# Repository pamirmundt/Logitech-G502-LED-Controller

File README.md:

# Logitech G502 Mouse with Python
A dirty code where you can set Logitech G502 mouse led color and read click/position events with Python. The USB packages send from the PC driver and mouse sniffed with USBlyzer software on a Windows machine. Attached demo codes tested only on a Raspberry Pi 3 (Raspbian). Sniffed files can be found under the USBlyzer folder. `interrupt.ulz` file has interrupt packages and `firstPlug.ulz` file has first time USB plug packages.

There are two interfaces under mouse:

#### Interface 0: Mouse Device
 - Get interrupt events (cursor move, click, wheel and etc.)

#### Interface 1: Keyboard Device (I guess)
 - Set RGB LED colors (Logo LED and DPI LED)

### Notes:
- Interrupt events should be read (Interface-0) continuously. Otherwise mouse buffer fills and you cannot send any more data to Interface-1.

## Board and Schematics
The system consists of 3 different boards: (1) Arduino UNO, (2)USB Host Shield 2.0 and (3)a custom LED controller/power supply board.

|     Layer     | Board Name                          | Board Description                   |
| ------------- | ----------------------------------- | ----------------------------------- |
|  1(bottom)    | Arduino UNO                         | MCU                                 |
|  2(middle)    | USB Host Shield 2.0                 | USB Controller in Host Mode         |
|  3(top)       | LED Controller and Power Supply (*) | RGB Led controller and 5V regulator |

(*) Eagle CAD files (.brd, .sch) can be found in the repo

## Future Improvements
- [ ] Switching regulator for 5V
- [ ] Single board layout
- [ ] Inconsistent color transitions between LED strip and G502 LEDs

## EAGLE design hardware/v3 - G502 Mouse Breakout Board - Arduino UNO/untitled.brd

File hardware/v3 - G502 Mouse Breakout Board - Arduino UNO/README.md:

## V3 G502 Breakout Board
- RGB Led Strip Controller Board for Arduino UNO
- 8-18V Input
- 5V regulator to supply Arduino UNO and USB Host Shield 2.0

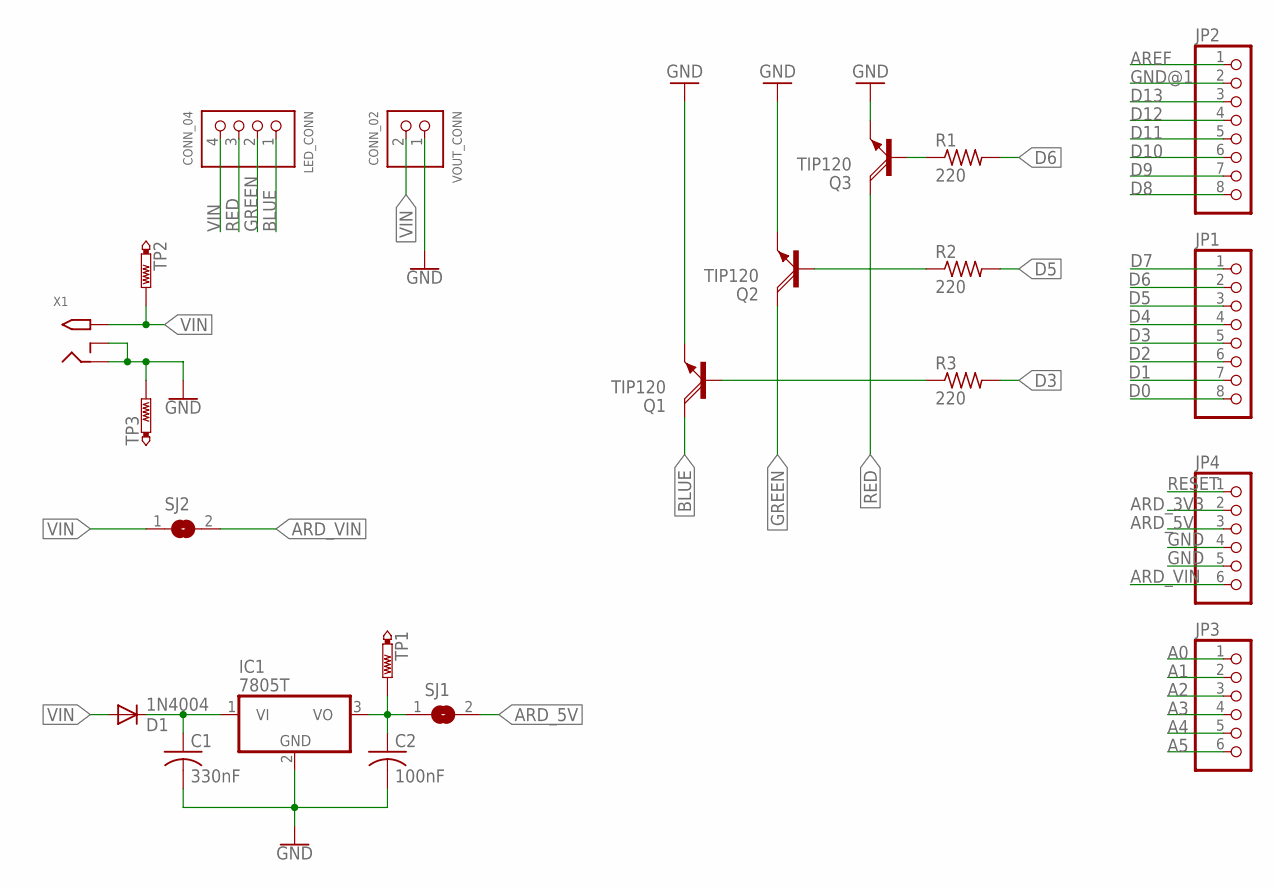
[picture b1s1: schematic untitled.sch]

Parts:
C1: 330nF; C050-035X075
C2: 100nF; C050-035X075
D1: 1N4004; DO41-10
IC1: 7805T; TO220H
JP1, JP2: PINHD-1X8; 1X08
JP3, JP4: PINHD-1X6; 1X06
LED_CONN: CONN_04; SCREWTERMINAL-5MM-4
Q1, Q2, Q3: TIP120; TO220AH
R1, R2, R3: 220; 0207/9
SJ1, SJ2: SJ
TP1, TP2, TP3: PTR1B1,27; B1,27
VOUT_CONN: CONN_02; SCREWTERMINAL-5MM-2
X1: 2.1MMJACKTHM; PJ-102A

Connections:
A0: JP3.1
A1: JP3.2
A2: JP3.3
A3: JP3.4
A4: JP3.5
A5: JP3.6
ARD_3V3: JP4.2
ARD_5V: JP4.3, SJ1.2
ARD_VIN: JP4.6, SJ2.2
AREF: JP2.1
BLUE: LED_CONN.1, Q1.C
D0: JP1.8
D1: JP1.7
D2: JP1.6
D3: JP1.5, R3.2
D4: JP1.4
D5: JP1.3, R2.2
D6: JP1.2, R1.2
D7: JP1.1
D8: JP2.8
D9: JP2.7
D10: JP2.6
D11: JP2.5
D12: JP2.4
D13: JP2.3
GND: C1.2, C2.2, IC1.2 (GND), JP4.4, JP4.5, Q1.E, Q2.E, Q3.E, TP3.TP, VOUT_CONN.1, X1.RING, X1.RING_SW
GND@1: JP2.2
GREEN: LED_CONN.2, Q2.C
unnamed: C1.1, D1.C, IC1.1 (VI)
unnamed: Q3.B, R1.1
unnamed: Q2.B, R2.1
unnamed: Q1.B, R3.1
RED: LED_CONN.3, Q3.C
REG_5V: C2.1, IC1.3 (VO), SJ1.1, TP1.TP
RESET: JP4.1
VIN: D1.A, LED_CONN.4, SJ2.1, TP2.TP, VOUT_CONN.2, X1.TIP

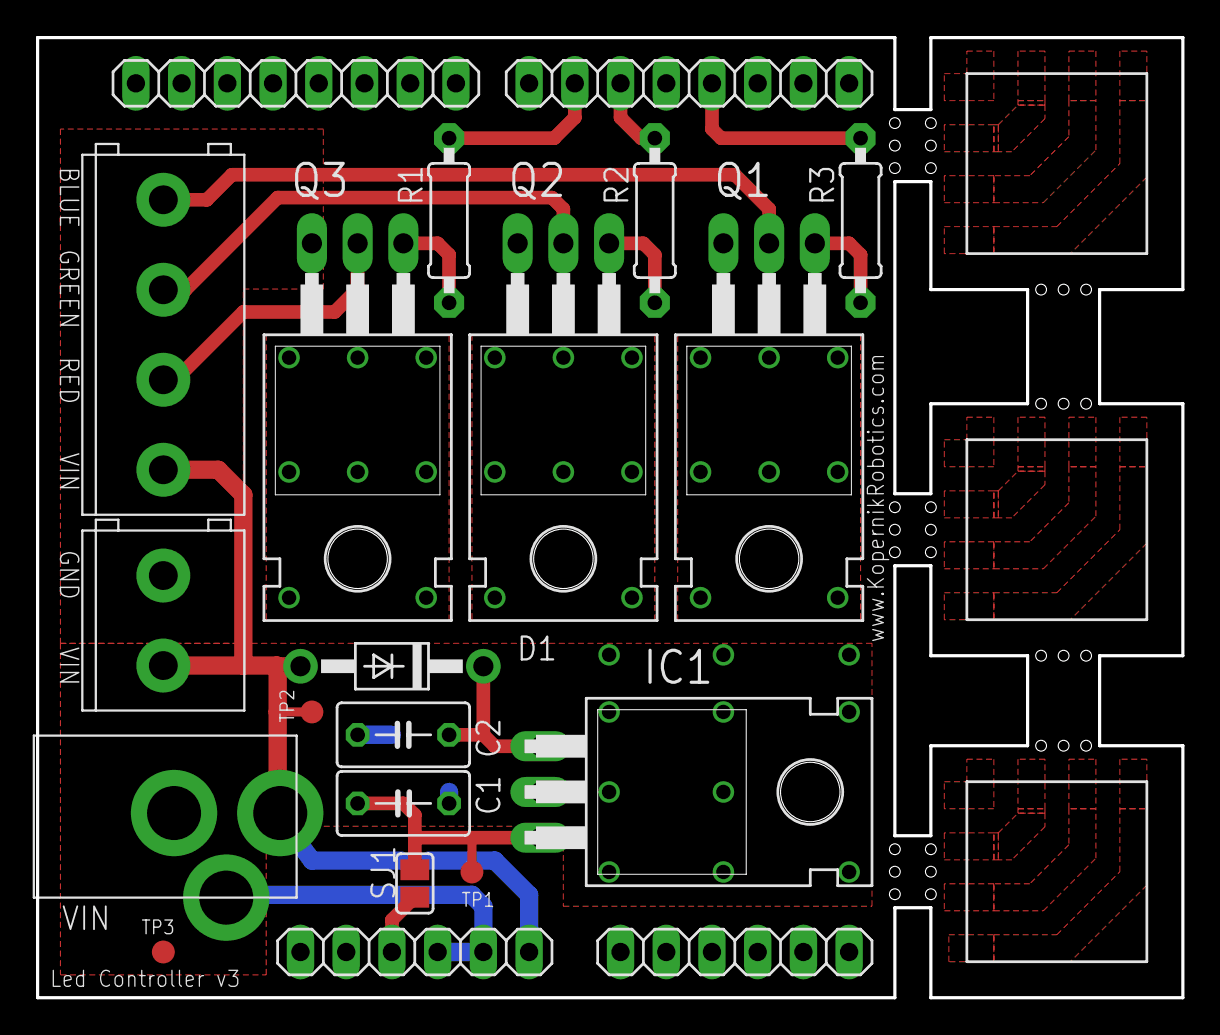
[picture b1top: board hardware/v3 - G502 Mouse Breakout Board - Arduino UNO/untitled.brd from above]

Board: 2 copper layers, 63.6 x 53.3 mm, 22 parts (1 on the bottom side), 15 nets.

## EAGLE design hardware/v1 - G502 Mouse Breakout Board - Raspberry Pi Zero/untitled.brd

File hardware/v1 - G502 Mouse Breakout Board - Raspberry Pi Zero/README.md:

## V1 G502 Breakout Board
- RGB Led Strip Controller Board for Raspberry Pi Zero

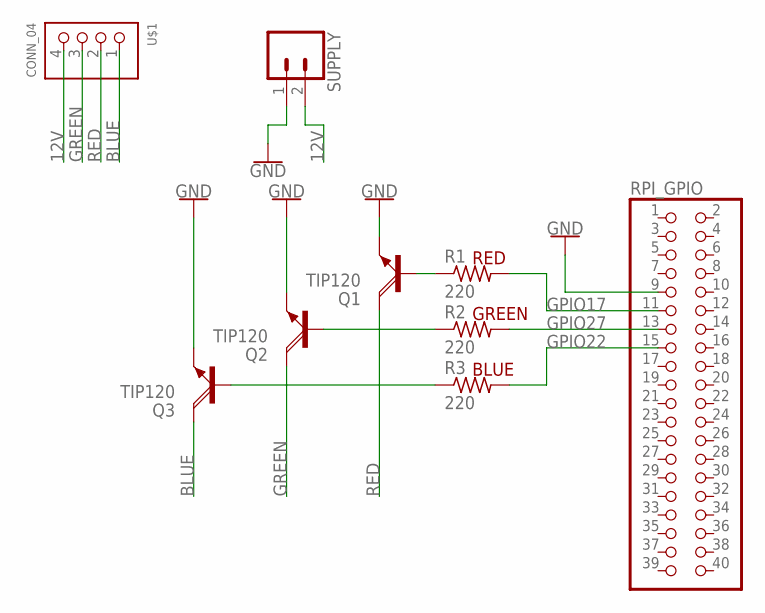
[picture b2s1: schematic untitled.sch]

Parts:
Q1, Q2, Q3: TIP120; TO220AH
R1, R2, R3: 220; 0207/10
RPI_GPIO: PINHD-2X20; 2X20
SUPPLY: CONN_025MM; SCREWTERMINAL-5MM-2
U$1: CONN_04; SCREWTERMINAL-5MM-4

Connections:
12V: SUPPLY.2, U$1.4
BLUE: Q3.C, U$1.1
GND: Q1.E, Q2.E, Q3.E, RPI_GPIO.9, SUPPLY.1
GPIO17: R1.2, RPI_GPIO.11
GPIO22: R3.2, RPI_GPIO.15
GPIO27: R2.2, RPI_GPIO.13
GREEN: Q2.C, U$1.3
unnamed: Q1.B, R1.1
unnamed: Q2.B, R2.1
unnamed: Q3.B, R3.1
RED: Q1.C, U$1.2

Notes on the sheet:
RED
GREEN
BLUE

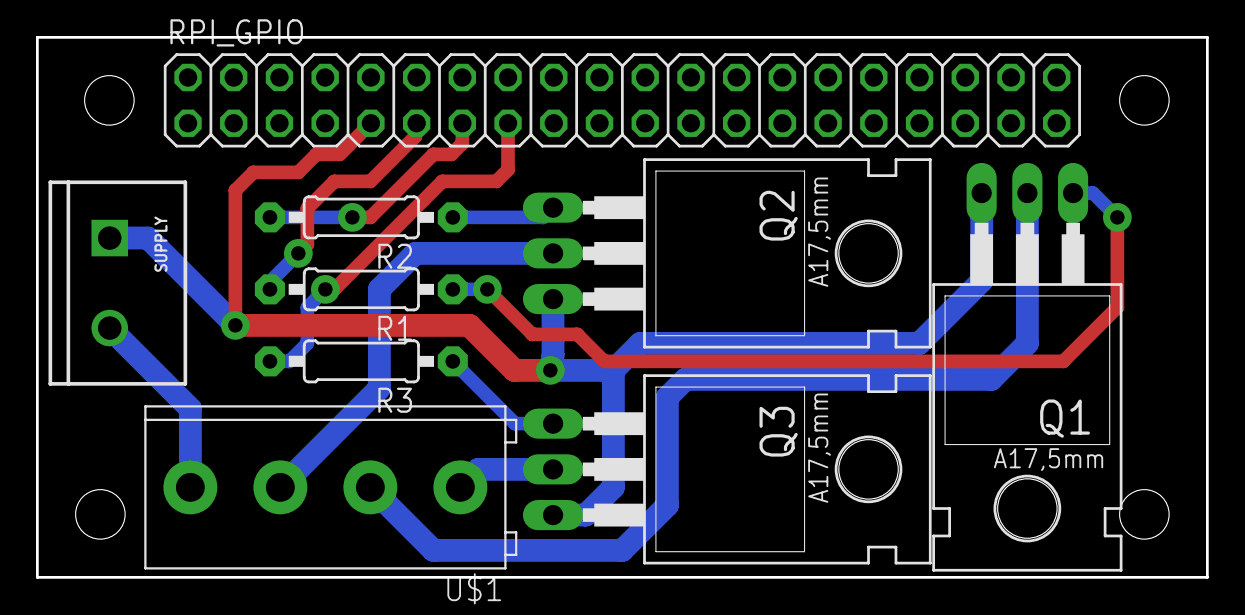
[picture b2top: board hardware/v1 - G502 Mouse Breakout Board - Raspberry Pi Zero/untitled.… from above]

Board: 2 copper layers, 65.0 x 30.0 mm, 9 parts (0 on the bottom side), 11 nets.

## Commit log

2019-03-06 init
2019-04-01 Arduino Example
2019-04-20 Board Schematics
2019-04-20 Create LICENSE

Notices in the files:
parts and their libraries:
SparkFun-Connectors: Licensing: Creative Commons ShareAlike 4.0 International - https://creativecommons.org/licenses/by-sa/4.0
